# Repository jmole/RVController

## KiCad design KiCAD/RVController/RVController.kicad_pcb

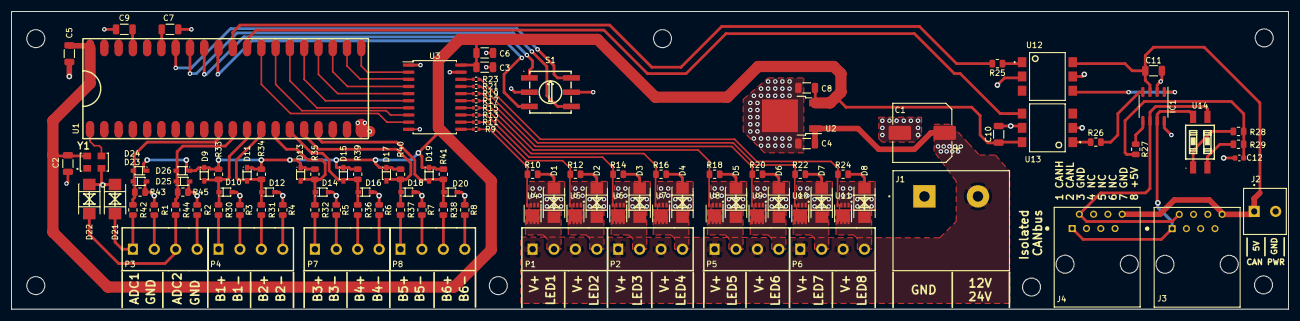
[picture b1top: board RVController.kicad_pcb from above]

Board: 2 copper layers, 227.2 x 53.0 mm, 119 parts (0 on the bottom side), 80 nets.

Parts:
C1: HZA107M050G24T-F; CP_Elec_10x10
C2, C3, C4, C8: 1206,100nF,50V,X7R; C_1206_3216Metric
C5, C6, C10, C11: 10UF; C_1206_3216Metric
C7, C9: 1206,1uF,50V,X7R; C_1206_3216Metric
C12: 4700pF; C_0603_1608Metric
D1, D2, D3, D4, D5, D6, D7, D8, D21, D22: SMBJ15CA-C78410; SMB_L4.6-W3.6-LS5.3-BI
D9, D10, D11, D12, D13, D14, D15, D16, D17, D18, D19, D20, D23, D24, D25, D26: SS16MH; SOD-323_L1.8-W1.3-LS2.5-RD
H1, H2, H3, H4, H5, H6, H7: MountingHole; MountingHole_3.2mm_M3_ISO14580
IC1: TJA1042T/1J; SO-8_3.9x4.9mm_P1.27mm
J1: 4-1437652-0; TE_4-1437652-0
J2: 284392-2; TE_284392-2
J3, J4: 54602-908LF; AMPHENOL_54602-908LF
P1, P2, P3, P4, P5, P6, P7, P8: WJ124-3_81-4P; CONN-TH_4P-P3.81_KF124-3.81-4P
R1, R2, R3, R4, R5, R6, R7, R8, R10, R12, R14, R16, R18, R20, R22, R24, R30, R31, R32, R36, R37, R38, R43, R45: 1K; R_0805_2012Metric
R9, R11, R13, R15, R17, R19, R21, R23: 0402,47; R_0402_1005Metric
R25, R26, R27: 300R; R_0805_2012Metric
R28, R29: 60R; R_0805_2012Metric
R33, R34, R35, R39, R40, R41: 22K; R_0805_2012Metric
R42, R44: 4.7K; R_0805_2012Metric
S1: MSDR-16S; SW-SMD_6P-L7.4-W7.4-P2.54-LS9.5-TL
U1: 114-83-640-41-134161
U2: CJ7805_3%; TO-252-2
U3: C554416; SOIC-20W_7.5x12.8mm_P1.27mm
U4, U5, U6, U7, U8, U9, U10, U11: AON7410; DFN-8_L3.0-W3.0-P0.65-BL
U12, U13: H11L1SR2M; IC_H11L1SR2M
U14: DSIC02LSGET; SW-SMD_4P-L6.0-W5.1-P2.54-LS9.3-BL
Y1: ECS-3961-240-AU-TR; OSC_ECS-3961-240-AU-TR

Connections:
+5V: C2.1, C3.1, C5.1, C6.1, C8.1, C10.1, D9.C, D11.C, D13.C, D15.C, D17.C, D19.C, D23.C, D25.C, R33.1, R34.1, R35.1, R39.1, R40.1, R41.1, U1.40 (VDD), U2.3 (Out), U3.20 (VCC), U13.6, Y1.4 (VDD)
+5V_CAN: C11.1, IC1.3 (VDD), J2.1, J3.8, J4.8, U12.6
/ADDR_1: S1.1, U1.32 (0.7)
/ADDR_2: S1.2, U1.33 (0.6)
/ADDR_4: S1.4, U1.31 (1.6)
/ADDR_8: S1.8, U1.34 (0.5)
/CAN_RX: U1.29 (15.5), U13.4
/CAN_TX: R25.2, U1.30 (15.4)
/CLK_IN: U1.1 (12.0), Y1.3 (OUTPUT)
ADC1: D23.A, D24.C, R42.2, R43.2, U1.10 (3.0)
ADC2: D25.A, D26.C, R44.2, R45.2, U1.11 (3.1)
BUTTON3: D9.A, D10.C, R30.2, R33.2, U1.12 (3.2)
BUTTON4: D11.A, D12.C, R31.2, R34.2, U1.13 (3.3)
BUTTON5: D13.A, D14.C, R32.2, R35.2, U1.14 (3.4)
BUTTON6: D15.A, D16.C, R36.2, R39.2, U1.15 (3.5)
BUTTON7: D17.A, D18.C, R37.2, R40.2, U1.16 (3.6)
BUTTON8: D19.A, D20.C, R38.2, R41.2, U1.17 (3.7)
CANH: IC1.7 (CANH), J3.1, J4.1, U14.4 (B1)
CANL: IC1.6 (CANL), J3.2, J4.2, U14.3 (B2)
GND: C1.2, C2.2, C3.2, C4.2, C5.2, C6.2, C7.1, C8.2, C9.1, C10.2, D1.1, D2.1, D3.1, D4.1, D5.1, D6.1, D7.1, D8.1, D10.A, D12.A, D14.A, D16.A, D18.A, D20.A, D21.1, D22.1, D24.A, D26.A, J1.1, R1.1, R2.1, R3.1, R4.1, R5.1, R6.1, R7.1, R8.1, R10.2, R12.2, R14.2, R16.2, R18.2, R20.2, R22.2, R24.2, R43.1, R45.1, S1.C, U1.20 (GND), U2.2 (GND), U3.1 (G1), U3.10 (GND), U3.19 (G2), U4.1 (S), U4.2 (S), U4.3 (S), U5.1 (S), U5.2 (S), U5.3 (S), U6.1 (S), U6.2 (S), U6.3 (S), U7.1 (S), U7.2 (S), U7.3 (S), U8.1 (S), U8.2 (S), U8.3 (S), U9.1 (S), U9.2 (S), U9.3 (S), U10.1 (S), U10.2 (S), U10.3 (S), U11.1 (S), U11.2 (S), U11.3 (S), U12.2, U13.5, Y1.2 (GND)
GND_CAN: C11.2, C12.2, IC1.2 (VSS), IC1.8 (STBY), J2.2, J3.3, J3.7, J4.3, J4.7, U12.5, U13.2
INPUT1: D21.2, P3.1, R42.1
INPUT2: D22.2, P3.3, R44.1
INPUT3: P4.1, R30.1
INPUT4: P4.3, R31.1
INPUT5: P7.1, R32.1
INPUT6: P7.3, R36.1
INPUT7: P8.1, R37.1
INPUT8: P8.3, R38.1
LED1: D1.2, P1.2, U4.5 (D), U4.6 (D), U4.7 (D), U4.8 (D), U4.9 (D)
LED2: D2.2, P1.4, U5.5 (D), U5.6 (D), U5.7 (D), U5.8 (D), U5.9 (D)
LED3: D3.2, P2.2, U6.5 (D), U6.6 (D), U6.7 (D), U6.8 (D), U6.9 (D)
LED4: D4.2, P2.4, U7.5 (D), U7.6 (D), U7.7 (D), U7.8 (D), U7.9 (D)
LED5: D5.2, P5.2, U8.5 (D), U8.6 (D), U8.7 (D), U8.8 (D), U8.9 (D)
LED6: D6.2, P5.4, U9.5 (D), U9.6 (D), U9.7 (D), U9.8 (D), U9.9 (D)
LED7: D7.2, P6.2, U10.5 (D), U10.6 (D), U10.7 (D), U10.8 (D), U10.9 (D)
LED8: D8.2, P6.4, U11.5 (D), U11.6 (D), U11.7 (D), U11.8 (D), U11.9 (D)
unnamed: C7.2, U1.35 (0.4)
unnamed: C9.2, U1.37 (0.2)
unnamed: C12.1, R27.2, R28.1, R29.2
unnamed: IC1.1 (TXD), U12.4
unnamed: IC1.4 (RXD), R26.2
unnamed: IC1.5 (SPLIT), R27.1
unnamed: P3.2, R1.2
unnamed: P3.4, R2.2
unnamed: P4.2, R3.2
unnamed: P4.4, R4.2
unnamed: P7.2, R5.2
unnamed: P7.4, R6.2
unnamed: P8.2, R7.2
unnamed: P8.4, R8.2
unnamed: R9.2, R10.1, U4.4 (G)
unnamed: R11.2, R12.1, U5.4 (G)
unnamed: R13.2, R14.1, U6.4 (G)
unnamed: R15.2, R16.1, U7.4 (G)
unnamed: R17.2, R18.1, U8.4 (G)
unnamed: R19.2, R20.1, U9.4 (G)
unnamed: R21.2, R22.1, U10.4 (G)
unnamed: R23.2, R24.1, U11.4 (G)
unnamed: R25.1, U12.1
unnamed: R26.1, U13.1
unnamed: R28.2, U14.1 (A1)
unnamed: R29.1, U14.2 (A2)
PWM1: R9.1, U3.11 (Y7)
PWM2: R11.1, U3.12 (Y6)
PWM3: R13.1, U3.13 (Y5)
PWM4: R15.1, U3.14 (Y4)
PWM5: R17.1, U3.15 (Y3)
PWM6: R19.1, U3.16 (Y2)
PWM7: R21.1, U3.17 (Y1)
PWM8: R23.1, U3.18 (Y0)
VBUS: C1.1, C4.1, J1.2, P1.1, P1.3, P2.1, P2.3, P5.1, P5.3, P6.1, P6.3, U2.1 (IN)
XPWM1: U1.28 (2.7), U3.9 (A7)
XPWM2: U1.27 (2.6), U3.8 (A6)
XPWM3: U1.26 (2.5), U3.7 (A5)
XPWM4: U1.25 (2.4), U3.6 (A4)
XPWM5: U1.24 (2.3), U3.5 (A3)
XPWM6: U1.23 (2.2), U3.4 (A2)
XPWM7: U1.22 (2.1), U3.3 (A1)
XPWM8: U1.21 (2.0), U3.2 (A0)

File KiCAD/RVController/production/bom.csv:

Designator,Footprint,Quantity,Value,LCSC Part #
U1,114-83-640-41-134161,1,114-83-640-41-134161 ,114-83-640-41-134161 
C3,C_1206_3216Metric,1,"1206,100nF,50V,X7R ",C24497
D23,SOD-323_L1.8-W1.3-LS2.5-RD,1,SS16MH,C364278
R4,R_0805_2012Metric,1,1K,RMCF0805JT1K00
D22,SMB_L4.6-W3.6-LS5.3-BI,1,SMBJ15CA-C78410,C78410
R29,R_0805_2012Metric,1,60R,RCS080560R4FKEA
D10,SOD-323_L1.8-W1.3-LS2.5-RD,1,SS16MH,C364278
D16,SOD-323_L1.8-W1.3-LS2.5-RD,1,SS16MH,C364278
R1,R_0805_2012Metric,1,1K,RMCF0805JT1K00
U12,IC_H11L1SR2M,1,H11L1SR2M,H11L1SR2M
P7,CONN-TH_4P-P3.81_KF124-3.81-4P,1,WJ124-3_81-4P,C69809
P6,CONN-TH_4P-P3.81_KF124-3.81-4P,1,WJ124-3_81-4P,C69809
P2,CONN-TH_4P-P3.81_KF124-3.81-4P,1,WJ124-3_81-4P,C69809
Y1,OSC_ECS-3961-240-AU-TR,1,ECS-3961-240-AU-TR,ECS-3961-240-AU-TR
U11,DFN-8_L3.0-W3.0-P0.65-BL,1,AON7410,C269266
D5,SMB_L4.6-W3.6-LS5.3-BI,1,SMBJ15CA-C78410,C78410
R26,R_0805_2012Metric,1,300R,RMCF0805JT300R
R37,R_0805_2012Metric,1,1K,RMCF0805JT1K00
C8,C_1206_3216Metric,1,"1206,100nF,50V,X7R ",C24497
R13,R_0402_1005Metric,1,"0402,47",C25118
C12,C_0603_1608Metric,1,4700pF,CGA3E2C0G1H472J080AA
D18,SOD-323_L1.8-W1.3-LS2.5-RD,1,SS16MH,C364278
C5,C_1206_3216Metric,1,10UF,CL31B106KAHNFNE
R43,R_0805_2012Metric,1,1K,RMCF0805JT1K00
C1,CP_Elec_10x10,1,HZA107M050G24T-F ,HZA107M050G24T-F
R12,R_0805_2012Metric,1,1K,RMCF0805JT1K00
S1,SW-SMD_6P-L7.4-W7.4-P2.54-LS9.5-TL,1,MSDR-16S,C411265
R19,R_0402_1005Metric,1,"0402,47",C25118
D6,SMB_L4.6-W3.6-LS5.3-BI,1,SMBJ15CA-C78410,C78410
D26,SOD-323_L1.8-W1.3-LS2.5-RD,1,SS16MH,C364278
P4,CONN-TH_4P-P3.81_KF124-3.81-4P,1,WJ124-3_81-4P,C69809
U4,DFN-8_L3.0-W3.0-P0.65-BL,1,AON7410,C269266
R35,R_0805_2012Metric,1,22K,RMCF0805JT22K0
U8,DFN-8_L3.0-W3.0-P0.65-BL,1,AON7410,C269266
R36,R_0805_2012Metric,1,1K,RMCF0805JT1K00
C10,C_1206_3216Metric,1,10UF,CL31B106KAHNFNE
R30,R_0805_2012Metric,1,1K,RMCF0805JT1K00
R11,R_0402_1005Metric,1,"0402,47",C25118
P3,CONN-TH_4P-P3.81_KF124-3.81-4P,1,WJ124-3_81-4P,C69809
R3,R_0805_2012Metric,1,1K,RMCF0805JT1K00
IC1,SO-8_3.9x4.9mm_P1.27mm,1,TJA1042T/1J,C53670
U6,DFN-8_L3.0-W3.0-P0.65-BL,1,AON7410,C269266
D9,SOD-323_L1.8-W1.3-LS2.5-RD,1,SS16MH,C364278
R31,R_0805_2012Metric,1,1K,RMCF0805JT1K00
D21,SMB_L4.6-W3.6-LS5.3-BI,1,SMBJ15CA-C78410,C78410
R39,R_0805_2012Metric,1,22K,RMCF0805JT22K0
R20,R_0805_2012Metric,1,1K,RMCF0805JT1K00
D13,SOD-323_L1.8-W1.3-LS2.5-RD,1,SS16MH,C364278
R15,R_0402_1005Metric,1,"0402,47",C25118
D17,SOD-323_L1.8-W1.3-LS2.5-RD,1,SS16MH,C364278
D8,SMB_L4.6-W3.6-LS5.3-BI,1,SMBJ15CA-C78410,C78410
R28,R_0805_2012Metric,1,60R,RCS080560R4FKEA
R18,R_0805_2012Metric,1,1K,RMCF0805JT1K00
U7,DFN-8_L3.0-W3.0-P0.65-BL,1,AON7410,C269266
R22,R_0805_2012Metric,1,1K,RMCF0805JT1K00
R21,R_0402_1005Metric,1,"0402,47",C25118
J4,AMPHENOL_54602-908LF,1,54602-908LF,54602-908LF
D12,SOD-323_L1.8-W1.3-LS2.5-RD,1,SS16MH,C364278
R40,R_0805_2012Metric,1,22K,RMCF0805JT22K0
D20,SOD-323_L1.8-W1.3-LS2.5-RD,1,SS16MH,C364278
J2,TE_284392-2,1,284392-2,284392-2
D2,SMB_L4.6-W3.6-LS5.3-BI,1,SMBJ15CA-C78410,C78410
C7,C_1206_3216Metric,1,"1206,1uF,50V,X7R ",C1848
D11,SOD-323_L1.8-W1.3-LS2.5-RD,1,SS16MH,C364278
D19,SOD-323_L1.8-W1.3-LS2.5-RD,1,SS16MH,C364278
R9,R_0402_1005Metric,1,"0402,47",C25118
U9,DFN-8_L3.0-W3.0-P0.65-BL,1,AON7410,C269266
R7,R_0805_2012Metric,1,1K,RMCF0805JT1K00
P5,CONN-TH_4P-P3.81_KF124-3.81-4P,1,WJ124-3_81-4P,C69809
P8,CONN-TH_4P-P3.81_KF124-3.81-4P,1,WJ124-3_81-4P,C69809
R5,R_0805_2012Metric,1,1K,RMCF0805JT1K00
R14,R_0805_2012Metric,1,1K,RMCF0805JT1K00
R42,R_0805_2012Metric,1,4.7K,RMCF0805JT4K70
R10,R_0805_2012Metric,1,1K,RMCF0805JT1K00
J3,AMPHENOL_54602-908LF,1,54602-908LF,54602-908LF
R17,R_0402_1005Metric,1,"0402,47",C25118
R23,R_0402_1005Metric,1,"0402,47",C25118
D14,SOD-323_L1.8-W1.3-LS2.5-RD,1,SS16MH,C364278
U13,IC_H11L1SR2M,1,H11L1SR2M,H11L1SR2M
U5,DFN-8_L3.0-W3.0-P0.65-BL,1,AON7410,C269266
R38,R_0805_2012Metric,1,1K,RMCF0805JT1K00
R41,R_0805_2012Metric,1,22K,RMCF0805JT22K0
R16,R_0805_2012Metric,1,1K,RMCF0805JT1K00
D15,SOD-323_L1.8-W1.3-LS2.5-RD,1,SS16MH,C364278
D1,SMB_L4.6-W3.6-LS5.3-BI,1,SMBJ15CA-C78410,C78410
U10,DFN-8_L3.0-W3.0-P0.65-BL,1,AON7410,C269266
R2,R_0805_2012Metric,1,1K,RMCF0805JT1K00
R32,R_0805_2012Metric,1,1K,RMCF0805JT1K00
D7,SMB_L4.6-W3.6-LS5.3-BI,1,SMBJ15CA-C78410,C78410
U14,SW-SMD_4P-L6.0-W5.1-P2.54-LS9.3-BL,1,DSIC02LSGET,C54949
R25,R_0805_2012Metric,1,300R,RMCF0805JT300R
C9,C_1206_3216Metric,1,"1206,1uF,50V,X7R ",C1848
R8,R_0805_2012Metric,1,1K,RMCF0805JT1K00
R33,R_0805_2012Metric,1,22K,RMCF0805JT22K0
D25,SOD-323_L1.8-W1.3-LS2.5-RD,1,SS16MH,C364278
C11,C_1206_3216Metric,1,10UF,CL31B106KAHNFNE
C2,C_1206_3216Metric,1,"1206,100nF,50V,X7R ",C24497
D24,SOD-323_L1.8-W1.3-LS2.5-RD,1,SS16MH,C364278
R27,R_0805_2012Metric,1,300R,RMCF0805JT300R
R6,R_0805_2012Metric,1,1K,RMCF0805JT1K00
C6,C_1206_3216Metric,1,10UF,CL31B106KAHNFNE
C4,C_1206_3216Metric,1,"1206,100nF,50V,X7R ",C24497
D3,SMB_L4.6-W3.6-LS5.3-BI,1,SMBJ15CA-C78410,C78410
P1,CONN-TH_4P-P3.81_KF124-3.81-4P,1,WJ124-3_81-4P,C69809
R44,R_0805_2012Metric,1,4.7K,RMCF0805JT4K70
R24,R_0805_2012Metric,1,1K,RMCF0805JT1K00
R45,R_0805_2012Metric,1,1K,RMCF0805JT1K00
U3,SOIC-20W_7.5x12.8mm_P1.27mm,1,C554416,C554416
D4,SMB_L4.6-W3.6-LS5.3-BI,1,SMBJ15CA-C78410,C78410
J1,TE_4-1437652-0,1,4-1437652-0,C60785
U2,TO-252-2,1,CJ7805_3%,C21706
R34,R_0805_2012Metric,1,22K,RMCF0805JT22K0

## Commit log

2022-08-04 Start project
2022-08-04 Adding freesoc part
2022-08-05 Getting started
    Added GaN NFET output channels, started work on input channels
2022-08-07 Basic layout done
2022-08-07 Almost done
    Added mounting holes, labels, etc.
2022-08-07 Done?
    Routed, etc. Exported STEP.
2022-08-08 Updated to SMD socket
2022-08-14 Updates to new parts, routed
    Changed to alternative FETs, Schottky diodes, TVS, etc. Ready for production
2022-08-14 Changes to DIP socket paste mask
2022-09-28 Production version
2023-04-26 Updates to controller PCB for production
2023-05-07 Updates to lighting controller
2023-06-19 Updates to light layout
2023-06-19 misc PCB changes
